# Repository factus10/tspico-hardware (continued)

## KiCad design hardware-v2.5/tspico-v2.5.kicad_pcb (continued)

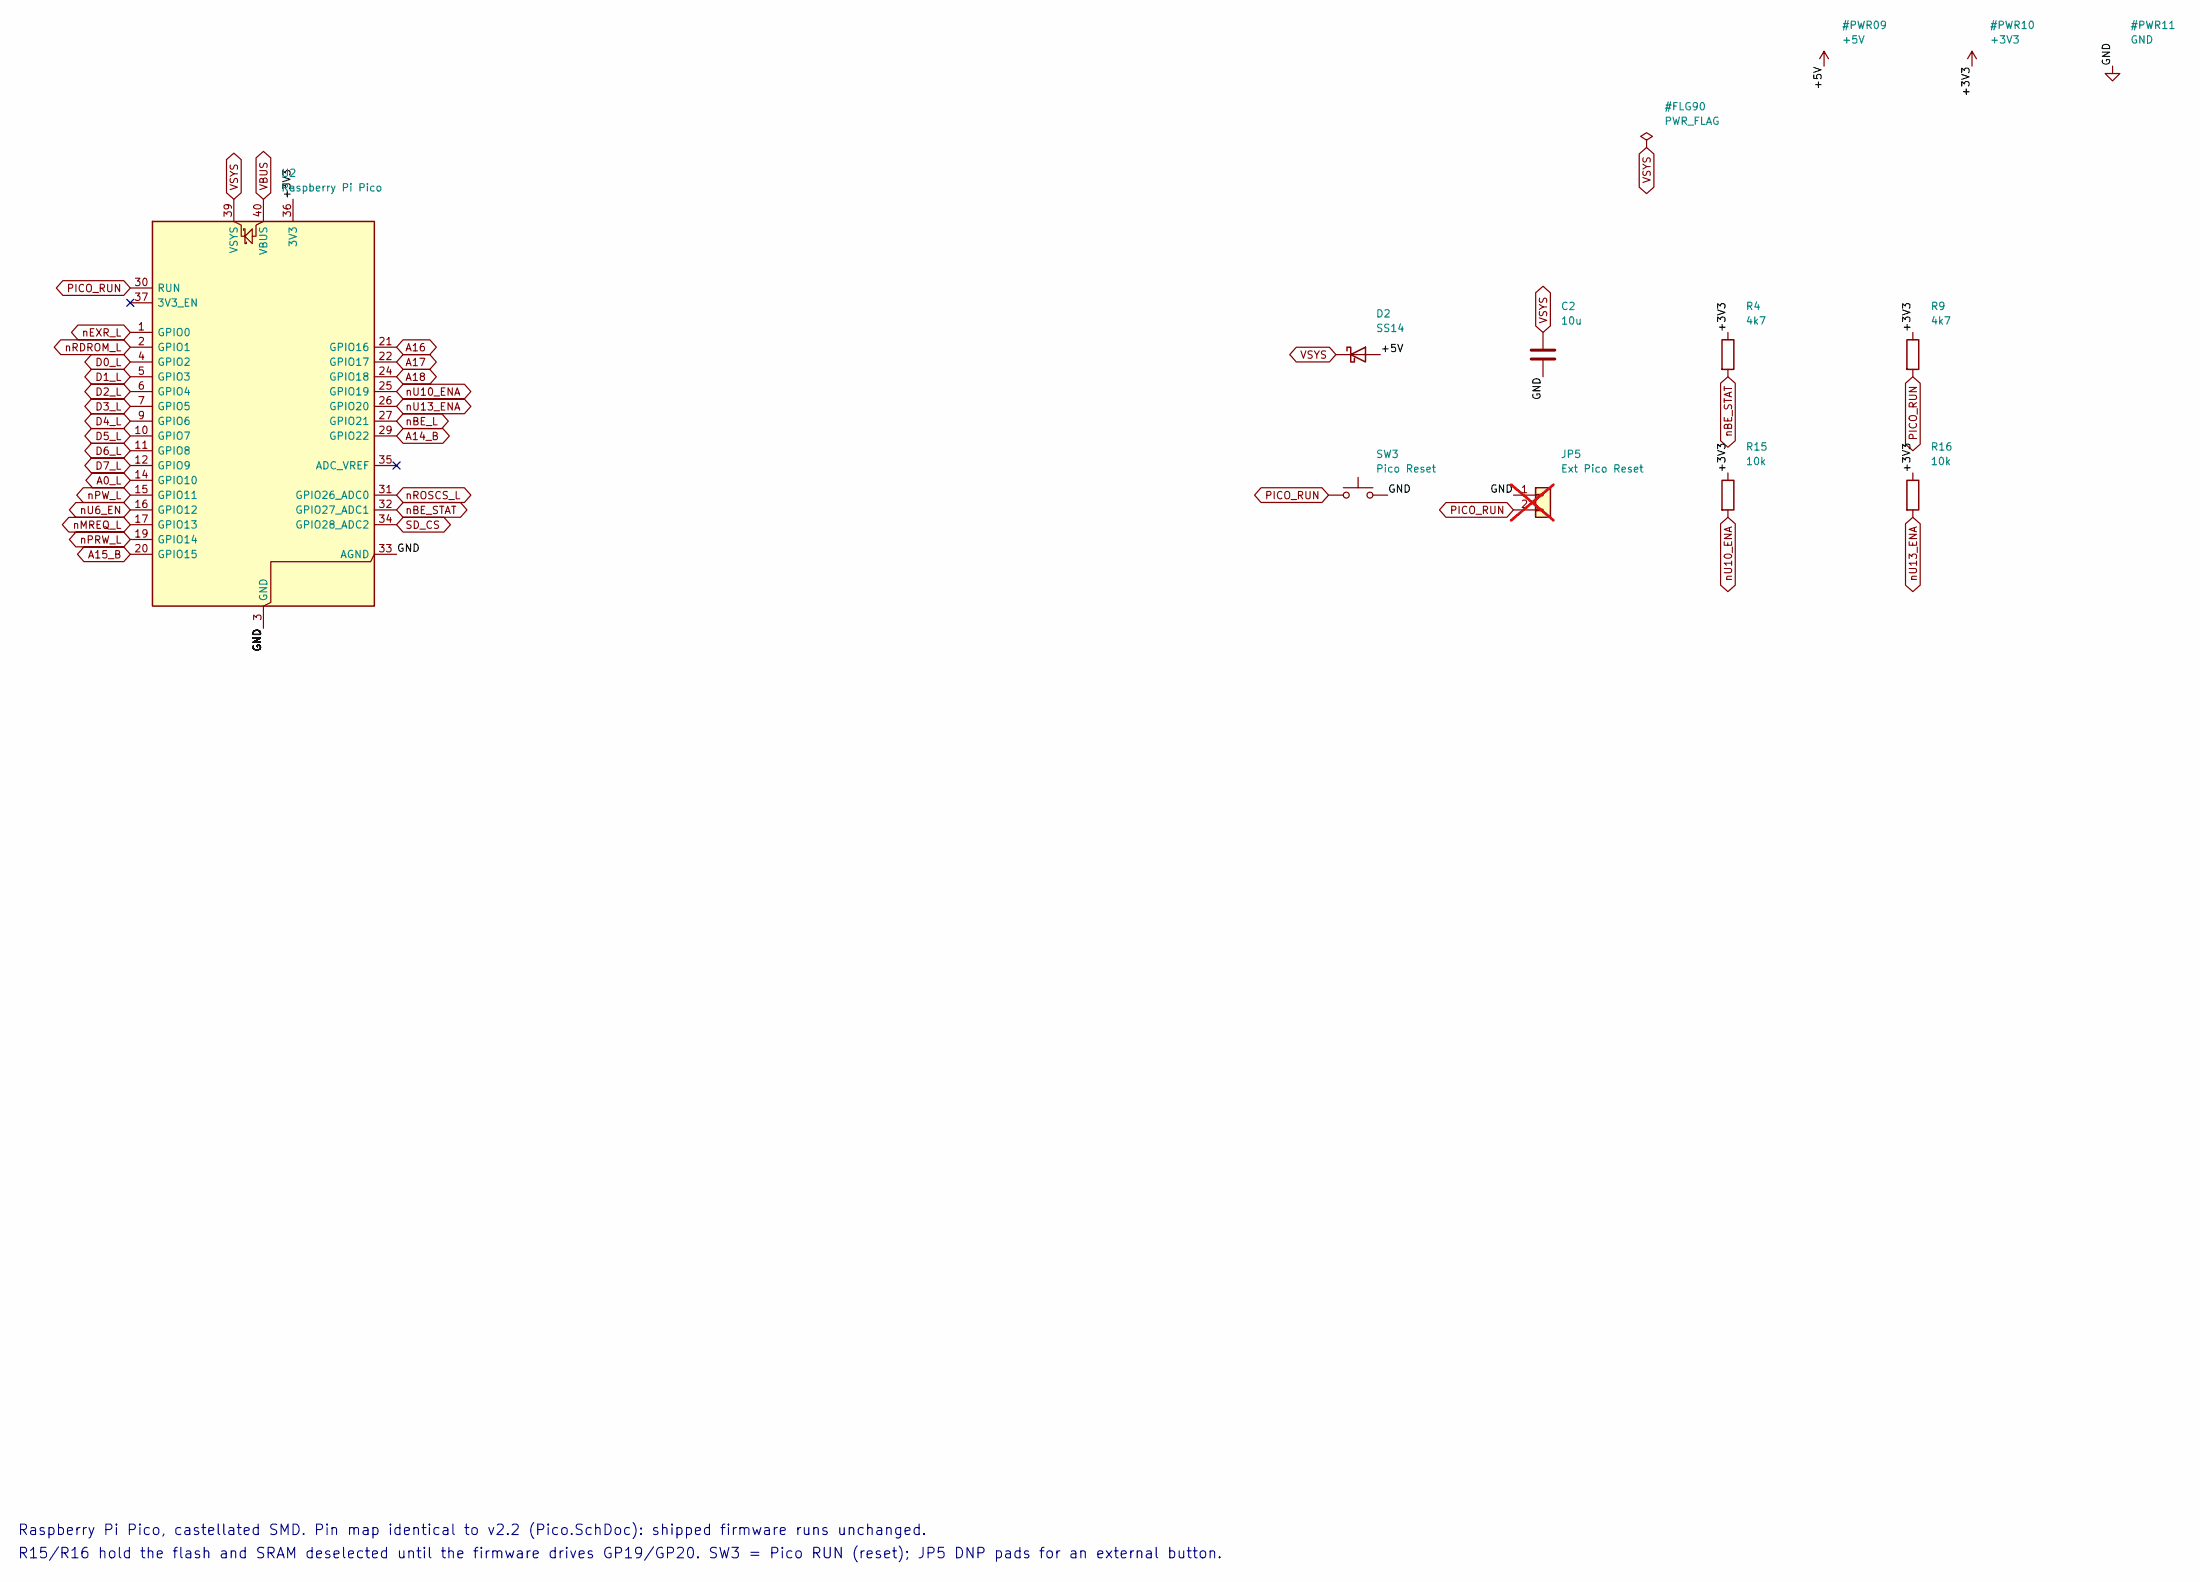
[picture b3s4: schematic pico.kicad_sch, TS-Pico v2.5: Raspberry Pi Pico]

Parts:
C2: 10u; C_0805_2012Metric; MPN CL21A106KAYNNNE; LCSC C15850
D2: SS14; D_SMA; MPN SS14; LCSC C2480
JP5: Ext Pico Reset; PinHeader_1x02_P2.54mm_Vertical_SMD_Pin1Left; not fitted
R4, R9: 4k7; R_0603_1608Metric; MPN 0603WAF4701T5E; LCSC C23162
R15, R16: 10k; R_0603_1608Metric; MPN 0603WAF1002T5E; LCSC C25804
SW3: Pico Reset; SW_Push_1P1T_XKB_TS-1187A; MPN TS-1187A-B-A-B; LCSC C318884
U2: Raspberry Pi Pico; RaspberryPi_Pico_SMD; MPN SC0915; LCSC C7203002

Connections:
+3V3: R4.1, R9.1, R15.1, R16.1, U2.36 (3V3); also elsewhere on the board
+5V: D2.2 (A); also elsewhere on the board
A0_L: U2.14 (GPIO10); also elsewhere on the board
A14_B: U2.29 (GPIO22); also elsewhere on the board
A15_B: U2.20 (GPIO15); also elsewhere on the board
A16: U2.21 (GPIO16); also elsewhere on the board
A17: U2.22 (GPIO17); also elsewhere on the board
A18: U2.24 (GPIO18); also elsewhere on the board
D0_L: U2.4 (GPIO2); also elsewhere on the board
D1_L: U2.5 (GPIO3); also elsewhere on the board
D2_L: U2.6 (GPIO4); also elsewhere on the board
D3_L: U2.7 (GPIO5); also elsewhere on the board
D4_L: U2.9 (GPIO6); also elsewhere on the board
D5_L: U2.10 (GPIO7); also elsewhere on the board
D6_L: U2.11 (GPIO8); also elsewhere on the board
D7_L: U2.12 (GPIO9); also elsewhere on the board
GND: C2.2, JP5.1, SW3.2, U2.3 (GND), U2.8 (GND), U2.13 (GND), U2.18 (GND), U2.23 (GND), U2.28 (GND), U2.33 (AGND), U2.38 (GND); also elsewhere on the board
PICO_RUN: JP5.2, R9.2, SW3.1, U2.30 (RUN)
SD_CS: U2.34 (GPIO28_ADC2); also elsewhere on the board
VBUS: U2.40 (VBUS); also elsewhere on the board
VSYS: C2.1, D2.1 (K), U2.39 (VSYS)
nBE_L: U2.27 (GPIO21); also elsewhere on the board
nBE_STAT: R4.2, U2.32 (GPIO27_ADC1); also elsewhere on the board
nEXR_L: U2.1 (GPIO0); also elsewhere on the board
nMREQ_L: U2.17 (GPIO13); also elsewhere on the board
nPRW_L: U2.19 (GPIO14); also elsewhere on the board
nPW_L: U2.15 (GPIO11); also elsewhere on the board
nRDROM_L: U2.2 (GPIO1); also elsewhere on the board
nROSCS_L: U2.31 (GPIO26_ADC0); also elsewhere on the board
nU6_EN: U2.16 (GPIO12); also elsewhere on the board
nU10_ENA: R15.2, U2.25 (GPIO19); also elsewhere on the board
nU13_ENA: R16.2, U2.26 (GPIO20); also elsewhere on the board

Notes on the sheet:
Raspberry Pi Pico, castellated SMD. Pin map identical to v2.2 (Pico.SchDoc): shipped firmware runs unchanged.
R15/R16 hold the flash and SRAM deselected until the firmware drives GP19/GP20. SW3 = Pico RUN (reset); JP5 DNP pads for an external button.

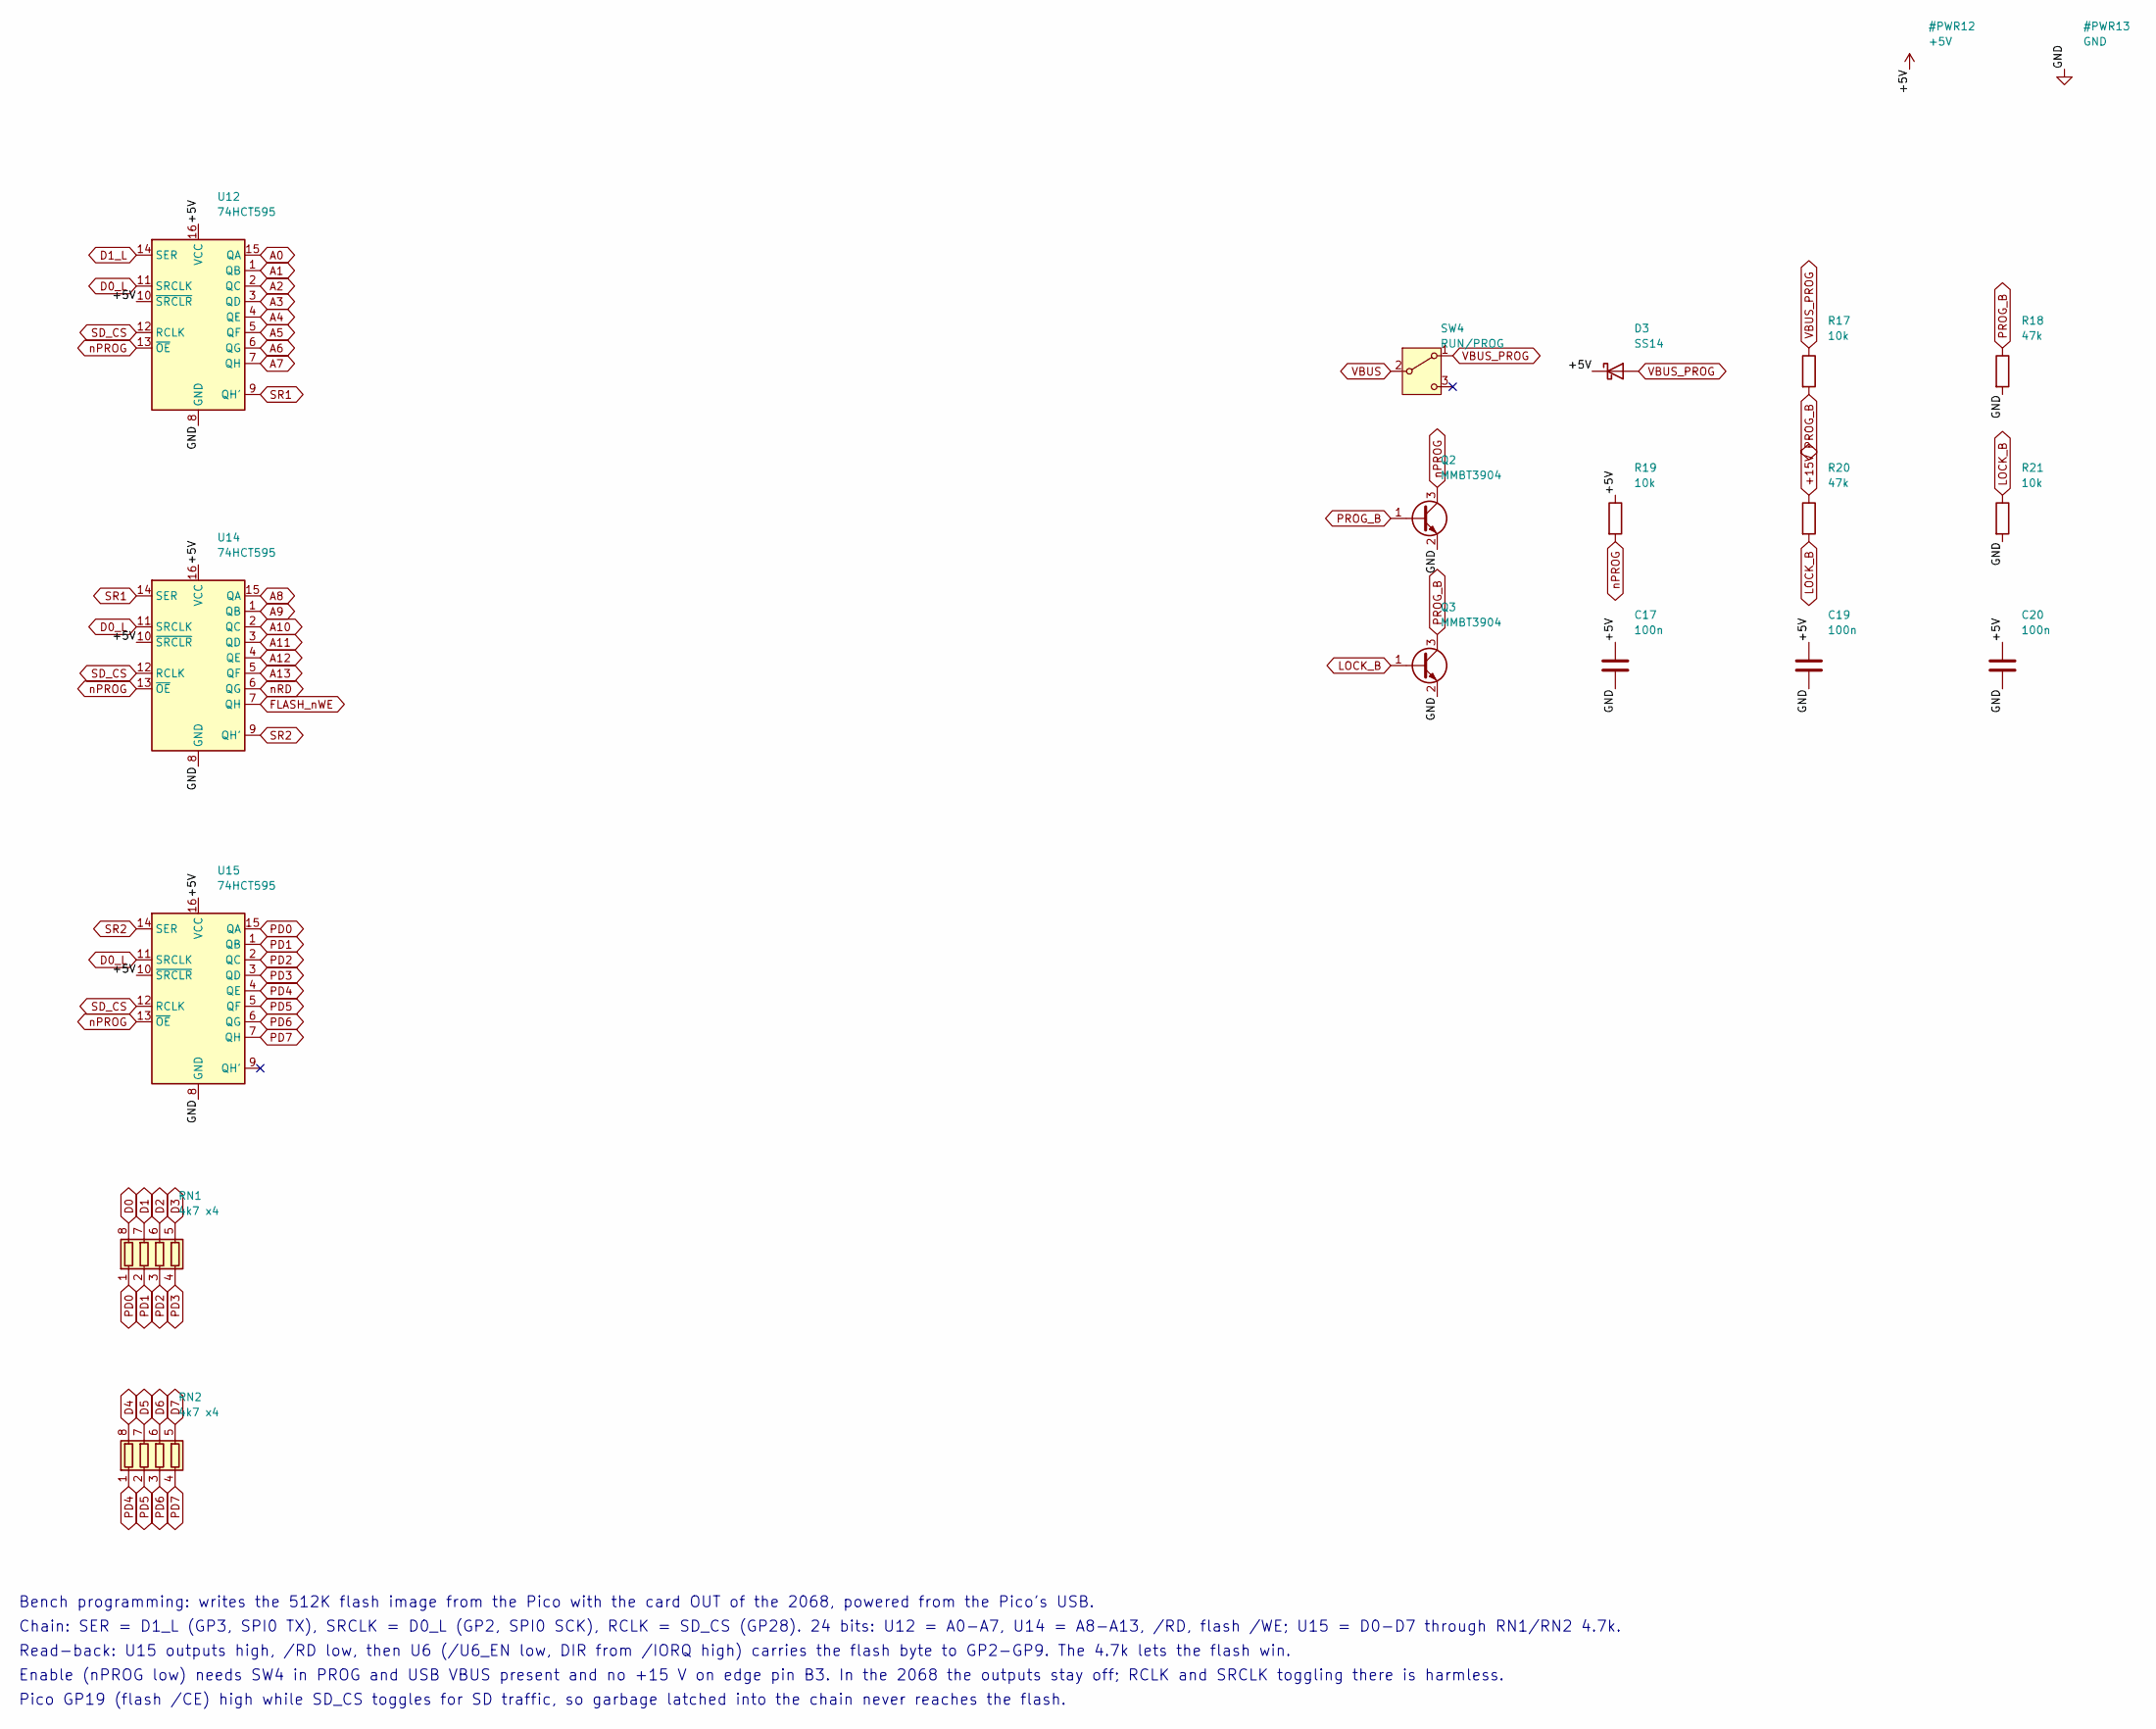
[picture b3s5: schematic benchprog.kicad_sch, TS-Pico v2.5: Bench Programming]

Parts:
C17, C19, C20: 100n; C_0603_1608Metric; MPN CC0603KRX7R9BB104; LCSC C14663
D3: SS14; D_SMA; MPN SS14; LCSC C2480
Q2, Q3: MMBT3904; SOT-23; MPN MMBT3904; LCSC C20526
R17, R19, R21: 10k; R_0603_1608Metric; MPN 0603WAF1002T5E; LCSC C25804
R18, R20: 47k; R_0603_1608Metric; MPN 0603WAF4702T5E; LCSC C25819
RN1, RN2: 4k7 x4; R_Array_Convex_4x0603; MPN 4D03WGJ0472T5E; LCSC C1980
SW4: RUN/PROG; SW_SPDT_Shouhan_MSK12C02; MPN MSK12C02; LCSC C431540
U12, U14, U15: 74HCT595; SOIC-16_3.9x9.9mm_P1.27mm; MPN 74HCT595D,118; LCSC C282339

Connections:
+5V: C17.1, C19.1, C20.1, D3.1 (K), R19.1, U12.10 (~SRCLR), U12.16 (VCC), U14.10 (~SRCLR), U14.16 (VCC), U15.10 (~SRCLR), U15.16 (VCC); also elsewhere on the board
+15V: R20.1; also elsewhere on the board
A0: U12.15 (QA); also elsewhere on the board
A1: U12.1 (QB); also elsewhere on the board
A2: U12.2 (QC); also elsewhere on the board
A3: U12.3 (QD); also elsewhere on the board
A4: U12.4 (QE); also elsewhere on the board
A5: U12.5 (QF); also elsewhere on the board
A6: U12.6 (QG); also elsewhere on the board
A7: U12.7 (QH); also elsewhere on the board
A8: U14.15 (QA); also elsewhere on the board
A9: U14.1 (QB); also elsewhere on the board
A10: U14.2 (QC); also elsewhere on the board
A11: U14.3 (QD); also elsewhere on the board
A12: U14.4 (QE); also elsewhere on the board
A13: U14.5 (QF); also elsewhere on the board
D0: RN1.8 (R1.2); also elsewhere on the board
D0_L: U12.11 (SRCLK), U14.11 (SRCLK), U15.11 (SRCLK); also elsewhere on the board
D1: RN1.7 (R2.2); also elsewhere on the board
D1_L: U12.14 (SER); also elsewhere on the board
D2: RN1.6 (R3.2); also elsewhere on the board
D3: RN1.5 (R4.2); also elsewhere on the board
D4: RN2.8 (R1.2); also elsewhere on the board
D5: RN2.7 (R2.2); also elsewhere on the board
D6: RN2.6 (R3.2); also elsewhere on the board
D7: RN2.5 (R4.2); also elsewhere on the board
FLASH_nWE: U14.7 (QH); also elsewhere on the board
GND: C17.2, C19.2, C20.2, Q2.2 (E), Q3.2 (E), R18.2, R21.2, U12.8 (GND), U14.8 (GND), U15.8 (GND); also elsewhere on the board
LOCK_B: Q3.1 (B), R20.2, R21.1
PD0: RN1.1 (R1.1), U15.15 (QA)
PD1: RN1.2 (R2.1), U15.1 (QB)
PD2: RN1.3 (R3.1), U15.2 (QC)
PD3: RN1.4 (R4.1), U15.3 (QD)
PD4: RN2.1 (R1.1), U15.4 (QE)
PD5: RN2.2 (R2.1), U15.5 (QF)
PD6: RN2.3 (R3.1), U15.6 (QG)
PD7: RN2.4 (R4.1), U15.7 (QH)
PROG_B: Q2.1 (B), Q3.3 (C), R17.2, R18.1
SD_CS: U12.12 (RCLK), U14.12 (RCLK), U15.12 (RCLK); also elsewhere on the board
SR1: U12.9 (QH'), U14.14 (SER)
SR2: U14.9 (QH'), U15.14 (SER)
VBUS: SW4.2 (B); also elsewhere on the board
VBUS_PROG: D3.2 (A), R17.1, SW4.1 (A)
nPROG: Q2.3 (C), R19.2, U12.13 (~OE), U14.13 (~OE), U15.13 (~OE)
nRD: U14.6 (QG); also elsewhere on the board

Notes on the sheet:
Bench programming: writes the 512K flash image from the Pico with the card OUT of the 2068, powered from the Pico's USB.
Chain: SER = D1_L (GP3, SPI0 TX), SRCLK = D0_L (GP2, SPI0 SCK), RCLK = SD_CS (GP28). 24 bits: U12 = A0-A7, U14 = A8-A13, /RD, flash /WE; U15 = D0-D7 through RN1/RN2 4.7k.
Read-back: U15 outputs high, /RD low, then U6 (/U6_EN low, DIR from /IORQ high) carries the flash byte to GP2-GP9. The 4.7k lets the flash win.
Enable (nPROG low) needs SW4 in PROG and USB VBUS present and no +15 V on edge pin B3. In the 2068 the outputs stay off; RCLK and SRCLK toggling there is harmless.
Pico GP19 (flash /CE) high while SD_CS toggles for SD traffic, so garbage latched into the chain never reaches the flash.

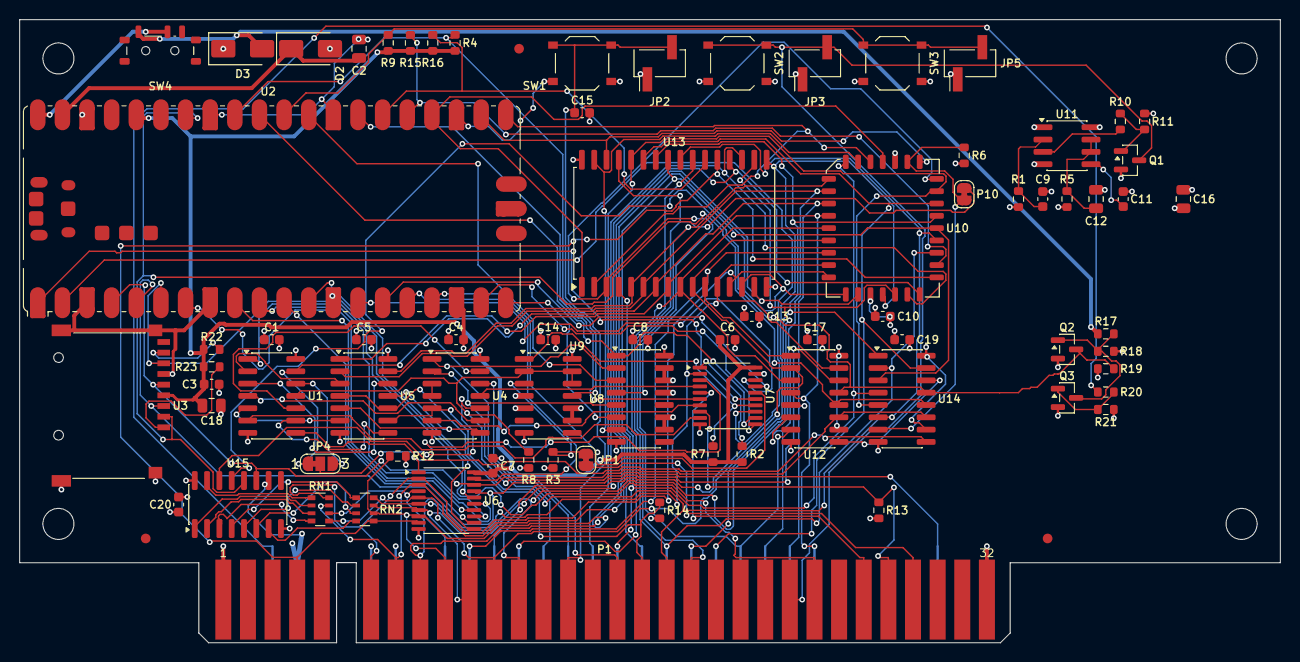
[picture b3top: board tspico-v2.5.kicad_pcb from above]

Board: 4 copper layers, 130.0 x 64.2 mm, 83 parts (0 on the bottom side), 109 nets.

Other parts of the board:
FID1, FID2, FID3: Fiducial_1mm_Mask2mm
H1, H2, H3, H4: MountingHole_3.2mm_M3

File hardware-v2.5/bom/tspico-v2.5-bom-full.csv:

"Value","Reference","Footprint","MPN","LCSC","Qty"
"100n","C1,C3-C11,C13-C15,C17,C19,C20","Capacitor_SMD:C_0603_1608Metric","CC0603KRX7R9BB104","C14663","16"
"10u","C2,C12,C16,C18","Capacitor_SMD:C_0805_2012Metric","CL21A106KAYNNNE","C15850","4"
"SS14","D2,D3","Diode_SMD:D_SMA","SS14","C2480","2"
"BE link","JP1","Jumper:SolderJumper-2_P1.3mm_Bridged_RoundedPad1.0x1.5mm","","","1"
"Port $00/$10","JP4","Jumper:SolderJumper-3_P1.3mm_Bridged12_RoundedPad1.0x1.5mm_NumberLabels","","","1"
"TS2068_Edge","P1","tspico:TS2068_EdgeConnector_2x32","","","1"
"Flash WE","P10","Jumper:SolderJumper-2_P1.3mm_Bridged_RoundedPad1.0x1.5mm","","","1"
"MMBT3904","Q1-Q3","Package_TO_SOT_SMD:SOT-23","MMBT3904","C20526","3"
"1M","R1","Resistor_SMD:R_0603_1608Metric","0603WAF1004T5E","C22935","1"
"4k7","R2,R4,R6-R10,R12","Resistor_SMD:R_0603_1608Metric","0603WAF4701T5E","C23162","8"
"2k7","R3","Resistor_SMD:R_0603_1608Metric","0603WAF2701T5E","C13167","1"
"220k","R5","Resistor_SMD:R_0603_1608Metric","0603WAF2203T5E","C22961","1"
"2k2","R11","Resistor_SMD:R_0603_1608Metric","0603WAF2201T5E","C4190","1"
"10k","R13-R17,R19,R21-R23","Resistor_SMD:R_0603_1608Metric","0603WAF1002T5E","C25804","9"
"47k","R18,R20","Resistor_SMD:R_0603_1608Metric","0603WAF4702T5E","C25819","2"
"4k7 x4","RN1,RN2","Resistor_SMD:R_Array_Convex_4x0603","4D03WGJ0472T5E","C1980","2"
"NMI","SW1","Button_Switch_SMD:SW_Push_1P1T_XKB_TS-1187A","TS-1187A-B-A-B","C318884","1"
"TS Reset","SW2","Button_Switch_SMD:SW_Push_1P1T_XKB_TS-1187A","TS-1187A-B-A-B","C318884","1"
"Pico Reset","SW3","Button_Switch_SMD:SW_Push_1P1T_XKB_TS-1187A","TS-1187A-B-A-B","C318884","1"
"RUN/PROG","SW4","Button_Switch_SMD:SW_SPDT_Shouhan_MSK12C02","MSK12C02","C431540","1"
"74LS04","U1","Package_SO:SOIC-14_3.9x8.7mm_P1.27mm","SN74LS04DR","C6796","1"
"Raspberry Pi Pico","U2","Module:RaspberryPi_Pico_SMD","SC0915","C7203002","1"
"microSD","U3","tspico:microSD_TF-01A","TF-01A","C91145","1"
"74LS32","U4","Package_SO:SOIC-14_3.9x8.7mm_P1.27mm","SN74LS32DR","C116812","1"
"74LS27","U5","Package_SO:SOIC-14_3.9x8.7mm_P1.27mm","XL74LS27","C707098","1"
"74LVC245APW","U6,U7","Package_SO:TSSOP-20_4.4x6.5mm_P0.65mm","74LVC245APW,118","C6082","2"
"74LS157","U8","Package_SO:SOIC-16_3.9x9.9mm_P1.27mm","XL74LS157","C707097","1"
"74LS09","U9","Package_SO:SOIC-14_3.9x8.7mm_P1.27mm","SN74LS09DR","C7731","1"
"SST39SF040","U10","Package_LCC:PLCC-32_11.4x14.0mm_P1.27mm","SST39SF040-55-4I-NHE-T","C632847","1"
"NE555","U11","Package_SO:SOIC-8_3.9x4.9mm_P1.27mm","NE555DR","C7593","1"
"74HCT595","U12,U14,U15","Package_SO:SOIC-16_3.9x9.9mm_P1.27mm","74HCT595D,118","C282339","3"
"CY62148ELL-55SXI","U13","Package_SO:SOP-32_11.305x20.495mm_P1.27mm","CY62148ELL-55SXIT","C511135","1"

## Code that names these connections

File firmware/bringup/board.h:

/*
 * TS-Pico v3 pin map, safe start-up and XL9555 expander access, shared by the
 * bring-up test and the ESP32 bridge.
 *
 * Pin map is taken from the schematic netlist (the hardware/ KiCad sheets), which
 * matches docs/v3-architecture.md section 7.
 */
#ifndef TSPICO_BOARD_H
#define TSPICO_BOARD_H

#include <stdbool.h>
#include <stdint.h>

#include "pico/types.h"

// ---- pins -------------------------------------------------------------------

#define PIN_MD0        0   // MD0-MD7 on GP0-GP7
#define PIN_NAEN_LO    8
#define PIN_NAEN_HI    9
#define PIN_NDATA_OE   10
#define PIN_BE_REQ     11
#define PIN_WAIT_REQ   12
#define PIN_Z80_A14    13  // GP13-GP22: inputs from U4 / U6
#define PIN_TAPE_IN    22
#define PIN_TAPE_OUT   23
#define PIN_I2C_SDA    24
#define PIN_I2C_SCL    25
#define PIN_RESET_HOLD 29
#define PIN_AUDIO_R    30
#define PIN_SD_MISO    32
#define PIN_OLED_DC    34
#define PIN_NIOX_INT   35
#define PIN_SD_CS      37
#define PIN_SD_SCK     38
#define PIN_SD_MOSI    39
#define PIN_OLED_CS    41
#define PIN_OLED_SCK   42
#define PIN_OLED_MOSI  43
#define PIN_WIFI_TX    44
#define PIN_WIFI_RX    45
#define PIN_AUDIO_L    46
#define PIN_PSRAM_CS   47

// ---- XL9555 expander (PCA9555 registers) ------------------------------------

#define IOX_ADDR 0x20
#define IOX_IN0  0
#define IOX_IN1  1
#define IOX_OUT0 2
#define IOX_POL1 5
#define IOX_CFG0 6
#define IOX_CFG1 7

// port 0, outputs
#define X_BUSRQ     (1u << 0)
#define X_NMI_REQ   (1u << 1)
#define X_NOLED_RST (1u << 2)
#define X_WIFI_EN   (1u << 3)
#define X_WIFI_DL   (1u << 4)
#define X_NLED      (1u << 5)
// port 1, inputs (all active low)
#define X_JOY_MASK  0x3f
#define X_NBUSAK    (1u << 6)
#define X_SD_CD     (1u << 7)

// Safe state: no bus request, no NMI, OLED in reset, ESP32 off, normal ESP32 boot,
// LED off. Bits 6-7 are spare (left as inputs).
#define IOX_OUT0_SAFE (X_NLED | 0xc0)

extern uint8_t iox_out0;
extern bool iox_present;

// The three 74LVC245s on the local bus (U1, U2, U3) have their /OE pins on
// GP8-GP10 with no external pull-up, and the RP2350 resets its pads with
// pull-downs on, so until firmware runs all three buffers are enabled. Call
// this first thing in main(); it turns them off.
void board_safe_init(void);

// Also starts the LED dimmer: D4 on R5 (100R) is very bright at full current,
// so the LED is switched at 100 Hz with a short on-time.
void iox_init(void);
int iox_write(uint8_t reg, uint8_t v);
int iox_read(uint8_t reg, uint8_t *v);
bool iox_set(uint8_t mask, bool on);

// D4. Use these rather than iox_set(X_NLED, ...); the dimmer owns that bit.
#define LED_BRIGHTNESS_DEFAULT 5   // percent
void led_set(bool on);
void led_brightness(uint percent);

#endif

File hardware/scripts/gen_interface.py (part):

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    bus_out = {  # pin -> (net, kind) for signals leaving the connector into logic on this sheet
        "A1": ("GND", "pwr"), "B1": ("GND", "pwr"), "A32": ("GND", "pwr"), "B32": ("GND", "pwr"),
        "B7": ("GND", "pwr"), "B8": ("GND", "pwr"), "B4": ("+5V_EDGE", OUT),
        "A2": ("EAR", "loc"), "B2": ("SPKR_TAPE", "loc"),
        "A4": ("D7", "loc"), "A7": ("D0", "loc"), "A8": ("D1", "loc"), "A9": ("D2", "loc"),
        "A10": ("D6", "loc"), "A11": ("D5", "loc"), "A12": ("D3", "loc"), "A13": ("D4", "loc"),
        "A14": ("nINT", "loc"), "A15": ("nNMI", "loc"), "A17": ("nMREQ", "loc"), "A18": ("nIORQ", "loc"),
        "A19": ("nRD", "loc"), "A20": ("nWR", "loc"), "A22": ("nWAIT", "loc"), "A23": ("nBUSRQ", "loc"),
        "A24": ("nRESET", "loc"), "A27": ("nEXROM", "loc"),
        "A28": ("nROSCS", "loc"), "A29": ("nBE", "loc"),
        "A21": ("nBUSAK", OUT), "A31": ("SOUND_2068", OUT),
        "B10": ("A0", "loc"), "B11": ("A1", "loc"), "B12": ("A2", "loc"), "B13": ("A3", "loc"),
        "B14": ("A15", "loc"), "B15": ("A14", "loc"), "B16": ("A13", "loc"), "B17": ("A12", "loc"),
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        s.label(f"A{idx}", U1.pin(f"B{b_}"))
        s.glabel(f"MD{idx}", U1.pin(f"A{b_}"), BI)
    s.label("GND", U1.pin("1"))                      # DIR low: B -> A
    s.glabel("nAEN_LO", U1.pin("19"), IN)
    s.label("+3V3", U1.pin("20")); s.label("GND", U1.pin("10"))

    U2 = transceiver("U2", 150, 110)
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        s.label(f"A{idx}", U2.pin(f"B{b_}"))
        s.glabel(f"MD{idx - 8}", U2.pin(f"A{b_}"), BI)
    s.label("GND", U2.pin("1"))
    s.glabel("nAEN_HI", U2.pin("19"), IN)
    s.label("+3V3", U2.pin("20")); s.label("GND", U2.pin("10"))

    # ---- U3 data transceiver ---------------------------------------------------------
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        s.label("DATA_DIR", U3.pin("1"))
    else:
        # A = Z80, B = MD. DIR = /RD: low on a Z80 read = B->A (local -> Z80).
        s.label("nRD", U3.pin("1"))
    s.glabel("nDATA_OE", U3.pin("19"), IN)
    s.label("+3V3", U3.pin("20")); s.label("GND", U3.pin("10"))

    # ---- U4 control inputs, fixed B (Z80) -> A (MCU), in finger order ----------
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    for k, (src, dst, pi, po) in enumerate(od_map):
        s.glabel(src, od[k].pin(pi), IN)
        s.label(dst, od[k].pin(po))
    s.glabel("WIFI_DL", od[5].pin("13"), IN); s.glabel("nWIFI_BOOT", od[5].pin("12"), OUT)   # ESP32 IO9, pulled up on the WiFi sheet

    if DMA_OPTION:
        # ---- U8 DMA bus drivers: 74LVC245, DIR high (A->B), /OE = nDMA_EN. DNP. ------
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
        # ---- U9 XOR: DATA_DIR = nRD xor nDMA_EN (fitted; nDMA_EN idles high) ---------
        U9 = s.place("74xGxx:74LVC1G86", "U9", "74LVC1G86", SOT23_5, 260, 250)
        s.label("nRD", U9.pin("1")); s.glabel("nDMA_EN", U9.pin("2"), IN); s.label("DATA_DIR", U9.pin("4"))
        s.label("+3V3", U9.pin("5")); s.label("GND", U9.pin("3"))
        R4 = s.place("Device:R", "R4", "10k", R0603, 290, 250)
        s.label("+3V3", R4.pin("1")); s.glabel("nDMA_EN", R4.pin("2"), IN)
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
    # ---- reset / NMI buttons, pull-down, tape divider --------------------------
    SW1 = s.place("Switch:SW_Push", "SW1", "TS Reset", SW_FP, 385, 150)
    s.label("nRESET", SW1.pin("1")); s.label("GND", SW1.pin("2"))
    SW2 = s.place("Switch:SW_Push", "SW2", "NMI", SW_FP, 385, 165)
    s.label("nNMI", SW2.pin("1")); s.label("GND", SW2.pin("2"))
    R1 = s.place("Device:R", "R1", "4k7", R0603, 380, 50)
    s.label("+3V3", R1.pin("1")); s.glabel("RESET_HOLD", R1.pin("2"), IN)
    R2 = s.place("Device:R", "R2", "4k7", R0603, 395, 90)
    s.glabel("TAPE_OUT", R2.pin("1"), IN); s.label("EAR", R2.pin("2"))
    R3 = s.place("Device:R", "R3", "1k", R0603, 395, 110)
    s.label("EAR", R3.pin("1")); s.label("GND", R3.pin("2"))
    s.text("R2/R3: TAPE_OUT divided to ~0.6 V for the 2068 EAR input.", 355, 125, 1.5)
    s.text("Values to be confirmed on the prototype.", 355, 128, 1.5)

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    # fetch right after a served byte (proto1 ran with a 2.2k bodge from A29 to +5V).
    # On +5V_EDGE so nothing feeds an unpowered 2068.
    R14 = s.place("Device:R", "R14", "2k2", R0603, 365, 195)
    s.glabel("+5V_EDGE", R14.pin("1"), IN); s.label("nBE", R14.pin("2"))
    # Buffer enables: the RP2350 resets its pads with pull-downs, which enabled U1, U2 and U3
    # together in reset and BOOTSEL (U1 and U2 both driving MD).
    for k, (ref, net) in enumerate((("R15", "nAEN_LO"), ("R16", "nAEN_HI"), ("R17", "nDATA_OE"))):
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
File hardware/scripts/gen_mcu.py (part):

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      12 MHz crystal with 15 pF loads and 1 k series, RUN pull-up and button,
      BOOTSEL button on QSPI_SS through 1 k, USB D+/D- 27 R series.
  U21 GD25Q128E (W25Q128 pinout) 16 MB QSPI flash on the QSPI bus (XIP, CS0)
  U22 APS6404L 8 MB PSRAM on the QSPI bus, CS1 = GPIO47
  J1  USB-C receptacle, data only: VBUS unconnected, 5.1 k Rd on CC1/CC2
  SW3 RUN, SW4 BOOTSEL, TP1-TP3 SWD pads
GPIO nets follow docs/v3-architecture.md section 7.
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        s.glabel(net, U.pin(by_name[f"GPIO{g}"]), shape)
    for g in SPARE:
        s.nc(U.pin(by_name[f"GPIO{g}"]))
    s.label("PSRAM_CS", U.pin(by_name["GPIO47"]))
    for num, nm in names.items():
        if nm in ("IOVDD", "QSPI_IOVDD", "USB_OTP_VDD", "ADC_AVDD", "VREG_VIN"):
            s.label("+3V3", U.pin(num))
        elif nm == "VREG_AVDD":
            s.label("VREG_AVDD", U.pin(num))
        elif nm in ("GND", "VREG_PGND"):
            s.label("GND", U.pin(num))
        elif nm == "DVDD":
            s.label("DVDD", U.pin(num))
    s.nc(U.pin(by_name["VREG_LX"]))                 # on-chip switcher unused: no inductor (datasheet fig. 24)
    s.label("GND", U.pin(by_name["VREG_FB"]))
    s.label("XIN", U.pin(by_name["XIN"])); s.label("XOUT", U.pin(by_name["XOUT"]))
    s.label("SWCLK", U.pin(by_name["SWCLK"])); s.label("SWDIO", U.pin(by_name["SWDIO"]))
    s.label("RUN", U.pin(by_name["RUN"]))
    s.label("USB_DM", U.pin(by_name["USB_DM"])); s.label("USB_DP", U.pin(by_name["USB_DP"]))
    for nm in ("QSPI_SD0", "QSPI_SD1", "QSPI_SD2", "QSPI_SD3", "QSPI_SCLK"):
        s.label(nm, U.pin(by_name[nm]))
    s.label("nQSPI_SS", U.pin(by_name["~{QSPI_SS}"]))

    # ---- core supply: external LDO on DVDD (RP2350 datasheet 6.3.7, figure 24) -------------
    # proto4: replaces L1 (Abracon AOTA-B201610S3R3-101-T, out of stock twice) and the on-chip
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    # for the 250 MHz bus clock (same choice as OpenSpand at 208 MHz).
    LDO = s.place("Regulator_Linear:ME6211C12M5", "U33", "ME6211C12M5G-N", SOT235, 250, 60)
    s.label("+3V3", LDO.pin("1")); s.label("GND", LDO.pin("2")); s.label("+3V3", LDO.pin("3"))
    s.nc(LDO.pin("4")); s.label("DVDD", LDO.pin("5"))
    for k, (ref, net, val, fp) in enumerate([("C53", "+3V3", "1u", C0603), ("C20", "DVDD", "4.7u", C0402), ("C22", "+3V3", "4.7u", C0402), ("C21", "DVDD", "100n", C0603), ("C47", "DVDD", "100n", C0603), ("C48", "DVDD", "100n", C0603)]):
        C = s.place("Device:C", ref, val, fp, 265 + 10 * k, 60)
        s.label(net, C.pin("1")); s.label("GND", C.pin("2"))
    s.text("U33 ME6211C12 (1.2 V, 300 mA) feeds DVDD; C53 its input, C20 its output. C22 at VREG_VIN (datasheet fig. 24). C21/C47/C48: 100 nF at DVDD pins 51, 32, 10.", 245, 75, 1.5)
    s.text("Firmware: set VREG.HIZ after boot (internal regulator draws ~400 uA until then); never use the regulator's low-power mode.", 245, 78, 1.5)
    R28 = s.place("Device:R", "R28", "33", R0603, 300, 85)
    s.label("+3V3", R28.pin("1")); s.label("VREG_AVDD", R28.pin("2"))
    C39 = s.place("Device:C", "C39", "4.7u", C0402, 315, 85)
    s.label("VREG_AVDD", C39.pin("1")); s.label("GND", C39.pin("2"))
    s.text("R28/C39: 33 R + 4.7 uF filter on VREG_AVDD (design guide R3/C9).", 245, 95, 1.5)
    FL2 = s.place("power:PWR_FLAG", "#FLG08", "PWR_FLAG", "", 330, 85)
    s.label("VREG_AVDD", FL2.pin("1"))

    # ---- IOVDD and analog decoupling: 12 x 100 nF ----------------------------------
    for k in range(9):
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
    # ---- crystal ---------------------------------------------------------------------
    Y1 = s.place("Device:Crystal_GND24", "Y1", "12MHz", "Crystal:Crystal_SMD_3225-4Pin_3.2x2.5mm", 270, 150)
    s.label("XIN", Y1.pin("1")); s.label("XOUT_R", Y1.pin("3")); s.label("GND", Y1.pin("2")); s.label("GND", Y1.pin("4"))
    R20 = s.place("Device:R", "R20", "1k", R0603, 295, 150)
    s.label("XOUT", R20.pin("1")); s.label("XOUT_R", R20.pin("2"))
    C35 = s.place("Device:C", "C35", "15p", C0603, 255, 165)
    s.label("XIN", C35.pin("1")); s.label("GND", C35.pin("2"))
    C36 = s.place("Device:C", "C36", "15p", C0603, 285, 165)
    s.label("XOUT_R", C36.pin("1")); s.label("GND", C36.pin("2"))
    s.text("Y1: 12 MHz, e.g. ABM8-272-T3 (CL 10 pF). C35/C36 15 pF, R20 1 k in series with XOUT.", 245, 180, 1.5)

    # ---- QSPI flash and PSRAM ---------------------------------------------------------
    F = s.place("Memory_Flash:W25Q128JVS", "U21", "GD25Q128ESIGR", "Package_SO:SOIC-8_5.3x5.3mm_P1.27mm", 340, 150)
    s.label("nQSPI_SS", F.pin("1")); s.label("QSPI_SD1", F.pin("2")); s.label("QSPI_SD2", F.pin("3")); s.label("GND", F.pin("4"))
    s.label("QSPI_SD0", F.pin("5")); s.label("QSPI_SCLK", F.pin("6")); s.label("QSPI_SD3", F.pin("7")); s.label("+3V3", F.pin("8"))
    P = s.place("Memory_RAM:APS6404L-3SQRx-SN", "U22", "APS6404L-3SQR-SN", "Package_SO:SOIC-8_3.9x4.9mm_P1.27mm", 340, 200, dnp=True)
    # APS6404L SOP-8: 1 CE#, 2 SO/SIO1, 3 SIO2, 4 VSS, 5 SI/SIO0, 6 SCLK, 7 SIO3, 8 VCC.
    # Package code SN is SOP-8L(150), 3.90 mm body (AP Memory outline; proto1 had the 208 mil footprint by mistake).
    # ESP-PSRAM64H / LY68L6400 (Adafruit 4677, the sanded "generic" PSRAM) have the same pinout and package.
    s.label("PSRAM_CS", P.pin("1")); s.label("QSPI_SD1", P.pin("2")); s.label("QSPI_SD2", P.pin("3")); s.label("GND", P.pin("4"))
    s.label("QSPI_SD0", P.pin("5")); s.label("QSPI_SCLK", P.pin("6")); s.label("QSPI_SD3", P.pin("7")); s.label("+3V3", P.pin("8"))
    for k, (ref, net) in enumerate([("C37", "+3V3"), ("C38", "+3V3")]):
        C = s.place("Device:C", ref, "100n", C0603, 375 + 10 * k, 175)
        s.label(net, C.pin("1")); s.label("GND", C.pin("2"))
    R21 = s.place("Device:R", "R21", "10k", R0603, 395, 150)
    s.label("+3V3", R21.pin("1")); s.label("nQSPI_SS", R21.pin("2"))
    s.text("U21 boot flash (XIP CS0). U22 PSRAM on the same QSPI bus, DNP (fit APS6404L-3SQR-SN or ESP-PSRAM64H; SD-image cache only),", 320, 225, 1.5)
    s.text("CS1 = GPIO47 (QMI CS1n). C37/C38 at U21/U22.", 320, 228, 1.5)

    # ---- RUN and BOOTSEL -------------------------------------------------------------
    R22 = s.place("Device:R", "R22", "10k", R0603, 250, 210)
    s.label("+3V3", R22.pin("1")); s.label("RUN", R22.pin("2"))
    SW3 = s.place("Switch:SW_Push", "SW3", "RUN", SW_FP, 270, 225)
    s.label("RUN", SW3.pin("1")); s.label("GND", SW3.pin("2"))
    R23 = s.place("Device:R", "R23", "1k", R0603, 250, 245)
    s.label("nQSPI_SS", R23.pin("1")); s.label("BOOTSEL_SW", R23.pin("2"))
    SW4 = s.place("Switch:SW_Push", "SW4", "BOOTSEL", SW_FP, 270, 260)
    s.label("BOOTSEL_SW", SW4.pin("1")); s.label("GND", SW4.pin("2"))

    # ---- USB-C, data only -----------------------------------------------------------
    J1 = s.place("Connector:USB_C_Receptacle_USB2.0_16P", "J1", "USB-C", "Connector_USB:USB_C_Receptacle_HRO_TYPE-C-31-M-12", 40, 60)
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        s.nc(J1.pin(pin))
    for pin in ("A1", "A12", "B1", "B12", "SH"):
        s.label("GND", J1.pin(pin))
    s.label("USB_DP_C", J1.pin("A6")); s.label("USB_DP_C", J1.pin("B6"))
    s.label("USB_DM_C", J1.pin("A7")); s.label("USB_DM_C", J1.pin("B7"))
    s.label("CC1", J1.pin("A5")); s.label("CC2", J1.pin("B5"))
    R24 = s.place("Device:R", "R24", "5k1", R0603, 80, 40)
    s.label("CC1", R24.pin("1")); s.label("GND", R24.pin("2"))
    R25 = s.place("Device:R", "R25", "5k1", R0603, 95, 40)
    s.label("CC2", R25.pin("1")); s.label("GND", R25.pin("2"))
    R26 = s.place("Device:R", "R26", "33", R0603, 80, 85)
    s.label("USB_DP_C", R26.pin("1")); s.label("USB_DP", R26.pin("2"))
    R27 = s.place("Device:R", "R27", "33", R0603, 95, 85)
    s.label("USB_DM_C", R27.pin("1")); s.label("USB_DM", R27.pin("2"))
    s.text("J1: USB 2.0. VBUS -> power sheet. SBU unconnected.", 20, 100, 1.5)
    s.text("R24/R25 5.1 k Rd. R26/R27 33 R series (JLC basic; 27 R is not).", 20, 103, 1.5)

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
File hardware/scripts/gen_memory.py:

#!/usr/bin/env python3
"""Generate memory.kicad_sch: slow I/O on a 16-bit I2C expander.

  U15  XL9555 (PCA9555 pinout, TSSOP-24, address 0x20) on I2C0 (GP24 SDA, GP25 SCL), /INT to GP35
       port 0 (outputs): BUSRQ, NMI_REQ, spare (OLED reset until proto3), WIFI_EN, WIFI_DL, nLED, SD_PWR_EN
       port 1 (inputs):  joystick x6, nBUSAK_L, SD_CD
  The expander powers up with every pin an input (100 k internal pull-ups), so the
  active-high outputs have 10 k pull-downs: nothing asserts until the firmware sets it.
  This replaces the 74HC273 CTL register, its power-on clear, and the STAT buffer.
  The address byte mux is now the two address 74LVC245s on the interface sheet.
"""
import os
import sys

sys.path.insert(0, os.path.dirname(os.path.abspath(__file__)))
from schlib import Sheet  # noqa: E402

TSSOP16 = "Package_SO:TSSOP-16_4.4x5mm_P0.65mm"
TSSOP24 = "Package_SO:TSSOP-24_4.4x7.8mm_P0.65mm"
R0603 = "Resistor_SMD:R_0603_1608Metric"
C0603 = "Capacitor_SMD:C_0603_1608Metric"
SOD123 = "Diode_SMD:D_SOD-123"

OUT, IN, BI = "output", "input", "bidirectional"


def main():
    s = Sheet("tspico-v3.kicad_sch", "memory.kicad_sch", "TS-Pico v3: I/O Expander")
    s.text("Slow control and status on one I2C expander. The fast local bus MD0-MD7 (address groups, Z80 data) is on the interface sheet.", 20, 285, 2.5)
    s.text("No flash or SRAM: the RP2350B serves memory from internal SRAM (PIO + DMA).", 20, 290, 2.0)

    s.power("+3V3", 300, 30, "#PWR04", flag=False)
    s.power("GND", 330, 40, "#PWR05", flag=False)

    U15 = s.place("Interface_Expansion:PCA9555PW", "U15", "XL9555", TSSOP24, 150, 110)
    port0 = ["BUSRQ", "NMI_REQ", None, "WIFI_EN", "WIFI_DL", "nLED", "SD_PWR_EN", None]           # pins 4-11
    port1 = ["JOY_UP", "JOY_DOWN", "JOY_LEFT", "JOY_RIGHT", "JOY_FIRE1", "JOY_FIRE2", "nBUSAK_L", "SD_CD"]   # pins 13-20
    for bit, net in enumerate(port0):
        pin = U15.pin(str(4 + bit))
        if net is None:
            s.nc(pin)
        elif net == "nLED":
            s.label(net, pin)
        else:
            s.glabel(net, pin, OUT)
    for bit, net in enumerate(port1):
        s.glabel(net, U15.pin(str(13 + bit)), IN)
    for pin in ("21", "2", "3"):                       # A0-A2 low: address 0x20
        s.label("GND", U15.pin(pin))
    s.glabel("I2C_SCL", U15.pin("22"), IN); s.glabel("I2C_SDA", U15.pin("23"), BI)
    s.glabel("nIOX_INT", U15.pin("1"), OUT)
    s.label("+3V3", U15.pin("24")); s.label("GND", U15.pin("12"))

    # I2C and /INT pull-ups
    for k, (ref, net, val) in enumerate((("R6", "I2C_SDA", "4k7"), ("R7", "I2C_SCL", "4k7"), ("R8", "nIOX_INT", "10k"))):
        R = s.place("Device:R", ref, val, R0603, 250 + 15 * k, 60)
        s.label("+3V3", R.pin("1")); s.glabel(net, R.pin("2"), BI)
    # power-up defaults for the active-high outputs (R11 held the SPI OLED in reset until proto3)
    for k, (ref, net) in enumerate((("R9", "BUSRQ"), ("R10", "NMI_REQ"), ("R12", "WIFI_EN"), ("R13", "WIFI_DL"))):
        R = s.place("Device:R", ref, "10k", R0603, 250 + 15 * k, 110)
        s.glabel(net, R.pin("1"), BI); s.label("GND", R.pin("2"))
    s.text("R9, R10, R12, R13: 10 k pull-downs beat the expander's 100 k pull-ups until the firmware configures the port.", 245, 125, 1.5)

    # activity LED, active low (the expander sinks better than it sources)
    R5 = s.place("Device:R", "R5", "100", R0603, 250, 160)
    s.label("+3V3", R5.pin("1")); s.label("LED_A", R5.pin("2"))
    D4 = s.place("Device:LED", "D4", "green", "LED_SMD:LED_0805_2012Metric", 270, 160)
    s.label("LED_A", D4.pin("A")); s.label("nLED", D4.pin("K"))
    s.text("R5/D4: activity LED, on when nLED is driven low.", 245, 175, 1.5)

    C = s.place("Device:C", "C10", "100n", C0603, 40, 255)
    s.label("+3V3", C.pin("1")); s.label("GND", C.pin("2"))

    s.write()
    print("wrote memory.kicad_sch")


if __name__ == "__main__":
    main()

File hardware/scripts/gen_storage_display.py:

#!/usr/bin/env python3
"""Generate storage_display.kicad_sch: micro SD socket and OLED header.

  J2  HRO TF-01A push-push micro SD (was Hirose DM3AT, 8x the price), SPI mode on SPI0, card detect to STAT
  U32 SY6280AAC current-limited load switch: the socket's VDD (+3V3_SD), on from expander P0.6 (SD_PWR_EN).
      Added for proto2 after issue #21: a card that latches up hits the switch's limit instead of pulling
      +3V3 down (which reset the RP2350B), and the firmware can power-cycle a wedged card. The card-side
      pull-ups are on +3V3_SD so they cannot power a switched-off card; the detect pull-up stays on +3V3.
  J3  4-pin header for a 1.54" 128x64 SSD1309 I2C OLED module (GND VCC SCL SDA) on I2C1, R44/R45 4k7 pull-ups.
      Proto3; proto1/2 had a 7-pin header for the Waveshare 1.27" 128x96 SSD1351 on SPI1.
"""
import os
import sys

sys.path.insert(0, os.path.dirname(os.path.abspath(__file__)))
from schlib import Sheet  # noqa: E402

R0603 = "Resistor_SMD:R_0603_1608Metric"
C0603 = "Capacitor_SMD:C_0603_1608Metric"
C0805 = "Capacitor_SMD:C_0805_2012Metric"
SD_FP = "tspico:microSD_TF-01A"   # custom footprint for the HRO TF-01A push-push socket (pads 1-8, 9 = CD switch, 10 = CD common, SH)
HDR4 = "Connector_PinHeader_2.54mm:PinHeader_1x04_P2.54mm_Vertical"

OUT, IN, BI = "output", "input", "bidirectional"


def main():
    s = Sheet("tspico-v3.kicad_sch", "storage_display.kicad_sch", "TS-Pico v3: SD and Display")
    s.text("Micro SD in SPI mode on the RP2350B SPI0 (GP36-GP39); card detect (switch to GND) into STAT bit 7.", 20, 285, 2.5)
    s.text("OLED: 4-pin header for a 1.54in 128x64 SSD1309 I2C module on I2C1 (GP42 SDA, GP43 SCL), its own bus so display updates never delay joystick reads.", 20, 290, 2.0)
    s.power("+3V3", 300, 30, "#PWR13", flag=False)
    s.power("GND", 330, 40, "#PWR14", flag=False)

    # ---- J2 micro SD ----------------------------------------------------------------
    J2 = s.place("Connector:Micro_SD_Card_Det_Hirose_DM3AT", "J2", "microSD", SD_FP, 100, 100)
    # SPI mode: DAT3 = CS, CMD = MOSI, CLK = SCK, DAT0 = MISO; DAT1/DAT2 pulled up and unused
    s.label("SD_DAT2", J2.pin("1")); s.label("SD_CS_J", J2.pin("2")); s.label("SD_MOSI_J", J2.pin("3"))
    s.glabel("+3V3_SD", J2.pin("4"), IN); s.label("SD_SCK_J", J2.pin("5")); s.label("GND", J2.pin("6"))
    s.label("SD_MISO_J", J2.pin("7")); s.label("SD_DAT1", J2.pin("8"))
    s.label("SD_CD_SW", J2.pin("9")); s.label("GND", J2.pin("10")); s.label("GND", J2.pin("SH"))
    # series resistors on the SPI lines (ringing on a long card trace), pull-ups per the SD spec
    for k, (ref, a, b) in enumerate((("R30", "SD_CS", "SD_CS_J"), ("R31", "SD_MOSI", "SD_MOSI_J"),
                                     ("R32", "SD_SCK", "SD_SCK_J"), ("R33", "SD_MISO", "SD_MISO_J"))):
        R = s.place("Device:R", ref, "33", R0603, 150 + 15 * k, 70)
        s.glabel(a, R.pin("1"), IN if a != "SD_MISO" else OUT); s.label(b, R.pin("2"))
    for k, (ref, net) in enumerate((("R34", "SD_CS_J"), ("R35", "SD_MISO_J"), ("R36", "SD_DAT1"), ("R37", "SD_DAT2"), ("R38", "SD_CD_SW"))):
        R = s.place("Device:R", ref, "10k", R0603, 150 + 15 * k, 130)
        if ref == "R38":                               # the detect switch must read with the card unpowered
            s.label("+3V3", R.pin("1"))
        else:
            s.glabel("+3V3_SD", R.pin("1"), IN)
        s.label(net, R.pin("2"))
    R39 = s.place("Device:R", "R39", "0", R0603, 230, 130)
    s.label("SD_CD_SW", R39.pin("1")); s.glabel("SD_CD", R39.pin("2"), OUT)
    for k, (ref, val, fp) in enumerate((("C50", "10u", C0603), ("C51", "100n", C0603))):
        C = s.place("Device:C", ref, val, fp, 100, 150 + 15 * k)
        s.glabel("+3V3_SD", C.pin("1"), IN); s.label("GND", C.pin("2"))

    # ---- U32 socket power switch -----------------------------------------------------
    # SY6280AAC (pin-compatible with the AAT4610-1: 1 OUT, 2 GND, 3 ISET, 4 EN active high, 5 IN).
    # I_LIM = 6800 / R_SET: 15k gives 0.45 A typ (0.34-0.57 A over the datasheet's +-25 %), above a
    # card's 200 mA peak, under what the TLV1117LV33 can give on top of the RP2350B.
    U32 = s.place("Power_Management:AAT4610BIGV-1-T1", "U32", "SY6280AAC", "Package_TO_SOT_SMD:SOT-23-5", 60, 200)
    s.label("+3V3", U32.pin("5")); s.glabel("+3V3_SD", U32.pin("1"), OUT); s.label("GND", U32.pin("2"))
    s.label("SD_ISET", U32.pin("3")); s.glabel("SD_PWR_EN", U32.pin("4"), IN)
    R42 = s.place("Device:R", "R42", "15k", R0603, 90, 215)
    s.label("SD_ISET", R42.pin("1")); s.label("GND", R42.pin("2"))
    R43 = s.place("Device:R", "R43", "10k", R0603, 105, 215)          # off until the firmware sets P0.6 (beats the expander's 100 k pull-up)
    s.glabel("SD_PWR_EN", R43.pin("1"), IN); s.label("GND", R43.pin("2"))
    C52 = s.place("Device:C", "C52", "1u", C0603, 40, 215)
    s.label("+3V3", C52.pin("1")); s.label("GND", C52.pin("2"))

    s.text("R30-R33 33 R series; R34-R37 10 k pull-ups (CS, MISO, DAT1, DAT2) on +3V3_SD; R38 pull-up on the detect switch (+3V3), R39 0 R link to SD_CD.", 90, 185, 1.5)
    s.text("Card present = SD_CD low (the TF-01A switch closes to GND; confirmed on proto1). U32: SD VDD switch, R42 sets 0.45 A, R43 holds it off.", 90, 188, 1.5)
    s.text("Firmware order: card detected, settle, SD_PWR_EN on, then SPI. SPI lines released (inputs) before SD_PWR_EN goes off.", 90, 191, 1.5)

    # ---- J3 OLED header --------------------------------------------------------------
    J3 = s.place("Connector_Generic:Conn_01x04", "J3", "OLED 1.54in 128x64 I2C", HDR4, 300, 110)
    nets = [("GND", "loc"), ("+3V3", "loc"), ("OLED_SCL", IN), ("OLED_SDA", BI)]
    for k, (net, kind) in enumerate(nets):
        at = J3.pin(str(k + 1))
        if kind == "loc":
            s.label(net, at)
        else:
            s.glabel(net, at, kind)
    # bus pull-ups on the card, so the bus idles high with no module or one without its own
    for k, (ref, net) in enumerate((("R44", "OLED_SCL"), ("R45", "OLED_SDA"))):
        R = s.place("Device:R", ref, "4k7", R0603, 330 + 15 * k, 150)
        s.label("+3V3", R.pin("1")); s.glabel(net, R.pin("2"), BI)
    s.text("J3 pin order matches the module: GND VCC SCL SDA. VCC is +3V3, so the module's own pull-ups stay at 3.3 V.", 280, 135, 1.5)

    s.write()
    print("wrote storage_display.kicad_sch")


if __name__ == "__main__":
    main()
